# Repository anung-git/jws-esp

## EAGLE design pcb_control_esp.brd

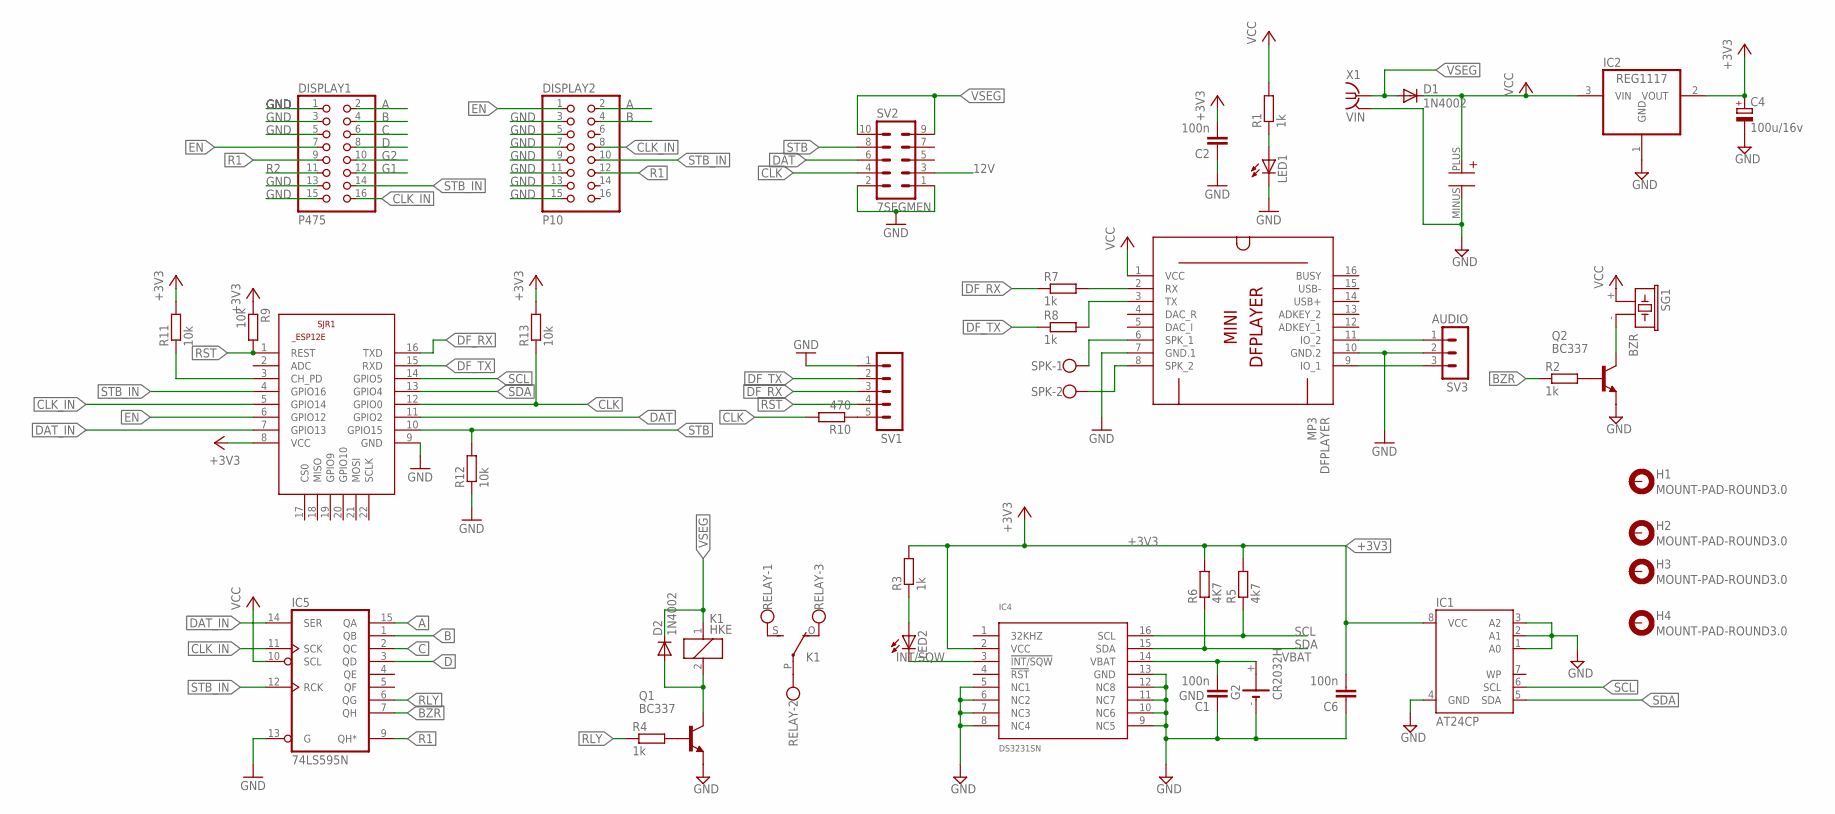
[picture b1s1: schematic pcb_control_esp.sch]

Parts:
C1, C2, C6: 100n; C025-024X044
C4: 100u/16v; E2,5-5
C24: 1000U; EEU-FR1C471B
D1, D2: 1N4002; DO35-10
DFPLAYER: MP3; DFPLAYER-MINI-MODULE
DISPLAY1: P475; 2X08
DISPLAY2: P10; 2X08
G2: CR2032H
H1, H2, H3, H4: MOUNT-PAD-ROUND3.0; 3,0-PAD
IC1: AT24CP; DIL08
IC2: REG1117; SOT223
IC4: DS3231SN; SO16W
IC5: 74LS595N; DIL16
K1: HKE; ZF112
LED1, LED2: LED3MM
Q1, Q2: BC337; TO92-EBC
R1, R2, R3, R4, R7, R8: 1k; 0207/7
R5: 4k7; 0207/7
R6: 4K7; 0207/7
R9, R11, R12, R13: 10k; 0207/7
R10: 470; 0207/7
RELAY: W237-103
SG1: BZR; F/CM12P
SJR1: ESP8266-12EESP12E; ESP8266-ESP12E
SPK: W237-102
SV1: MA05-1
SV2: 7SEGMEN; MA05-2
SV3: AUDIO; MA03-1
X1: VIN; J502-ND

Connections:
12V: SV2.3
+3V3: C2.2, C4.+, C6.2, IC1.8 (VCC), IC2.2 (VOUT), IC4.2 (VCC), R3.2, R5.2, R6.2, R9.1, R11.2, R13.2, SJR1.8 (VCC)
A: DISPLAY1.2, DISPLAY2.2, IC5.15 (QA)
B: DISPLAY1.4, DISPLAY2.4, IC5.1 (QB)
BZR: IC5.7 (QH), R2.1
C: DISPLAY1.6, IC5.2 (QC)
CLK: R10.2, R13.1, SJR1.12 (GPIO0), SV2.4
CLK_IN: DISPLAY1.16, DISPLAY2.8, IC5.11 (SCK), SJR1.5 (GPIO14)
D: DISPLAY1.8, IC5.3 (QD)
DAT: SJR1.11 (GPIO2), SV2.6
DAT_IN: IC5.14 (SER), SJR1.7 (GPIO13)
DF_RX: R7.1, SJR1.16 (TXD), SV1.3
DF_TX: R8.1, SJR1.15 (RXD), SV1.2
EN: DISPLAY1.7, DISPLAY2.1, SJR1.6 (GPIO12)
G1: DISPLAY1.12
G2: DISPLAY1.10
GND: C1.1, C2.1, C4.-, C6.1, C24.MINUS, DFPLAYER.7 (GND.1), DFPLAYER.10 (GND.2), DISPLAY1.1, DISPLAY1.3, DISPLAY1.5, DISPLAY1.13, DISPLAY1.15, DISPLAY2.3, DISPLAY2.5, DISPLAY2.7, DISPLAY2.9, DISPLAY2.11, DISPLAY2.13, DISPLAY2.15, G2.-, IC1.1 (A0), IC1.2 (A1), IC1.3 (A2), IC1.4 (GND), IC2.1 (GND), IC4.5 (NC1), IC4.6 (NC2), IC4.7 (NC3), IC4.8 (NC4), IC4.9 (NC5), IC4.10 (NC6), IC4.11 (NC7), IC4.12 (NC8), IC4.13 (GND), IC5.8 (GND), IC5.13 (G), LED1.K (C), Q1.E, Q2.E, R12.1, SJR1.9 (GND), SV1.1, SV2.1, SV2.2, SV3.2, X1.2, X1.5 (2)
INT/SQW: IC4.3 (!INT/SQW), LED2.K (C)
unnamed: Q2.B, R2.2
unnamed: Q2.C, SG1.- (2)
unnamed: LED2.A, R3.1
unnamed: K1.O, RELAY.3
unnamed: R11.1, SJR1.3 (CH_PD)
unnamed: Q1.B, R4.2
unnamed: LED1.A, R1.1
unnamed: DFPLAYER.2 (RX), R7.2
unnamed: DFPLAYER.3 (TX), R8.2
unnamed: D2.A, K1.2, Q1.C
unnamed: R10.1, SV1.5
unnamed: K1.S, RELAY.1
unnamed: K1.P, RELAY.2
unnamed: DFPLAYER.6 (SPK_1), SPK.1
unnamed: DFPLAYER.8 (SPK_2), SPK.2
unnamed: DFPLAYER.9 (IO_1), SV3.3
unnamed: DFPLAYER.11 (IO_2), SV3.1
R1: DISPLAY1.9, DISPLAY2.12, IC5.9 (QH*)
R2: DISPLAY1.11
RLY: IC5.6 (QG), R4.1
RST: R9.2, SJR1.1 (REST), SV1.4
SCL: IC1.6 (SCL), IC4.16 (SCL), R5.1, SJR1.14 (GPIO5)
SDA: IC1.5 (SDA), IC4.15 (SDA), R6.1, SJR1.13 (GPIO4)
STB: R12.2, SJR1.10 (GPIO15), SV2.8
STB_IN: DISPLAY1.14, DISPLAY2.10, IC5.12 (RCK), SJR1.4 (GPIO16)
VBAT: C1.2, G2.+, IC4.14 (VBAT)
VCC: C24.PLUS, D1.C, DFPLAYER.1 (VCC), IC2.3 (VIN), IC5.10 (SCL), IC5.16 (VCC), R1.2, SG1.+ (1)
VSEG: D1.A, D2.C, K1.1, SV2.9, SV2.10, X1.3 (1), X1.4 (1)

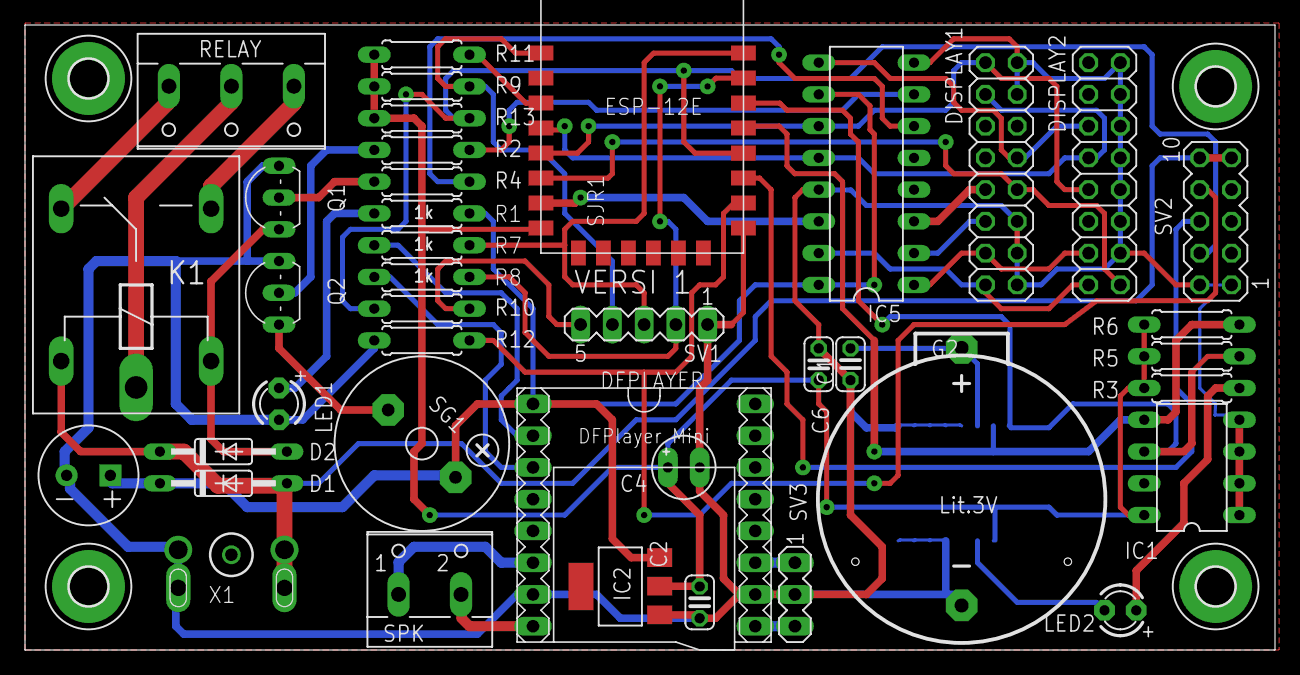
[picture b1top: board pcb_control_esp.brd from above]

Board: 2 copper layers, 100.0 x 50.0 mm, 45 parts (1 on the bottom side), 42 nets.

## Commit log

2019-09-01 upload file
2019-09-01 tambah lib esp
2019-09-01 ganti nama
2019-09-01 finish
2019-09-01 pindah jalur downloader
2020-09-20 swap i2c

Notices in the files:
parts and their libraries:
diy-modules: Released under the Creative Commons Attribution 4.0 International License: http://creativecommons.org/licenses/by/4.0
